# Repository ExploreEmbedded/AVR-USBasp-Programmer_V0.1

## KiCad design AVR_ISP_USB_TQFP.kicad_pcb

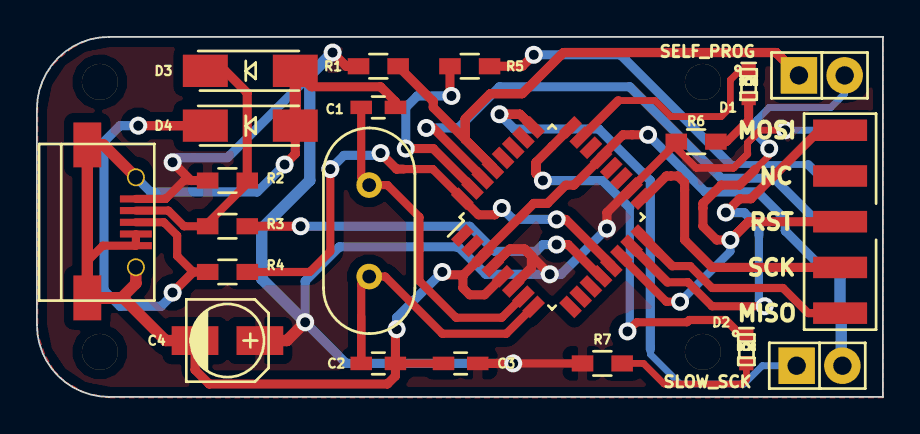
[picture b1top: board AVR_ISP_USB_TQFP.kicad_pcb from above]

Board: 2 copper layers, 47.0 x 20.0 mm, 26 parts (1 on the bottom side), 21 nets.

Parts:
C1, C2: 22pF; C_0603_HandSoldering
C3: 0.1uF; C_0603_HandSoldering
C4: 4.7uF; c_elec_4x5.8
CON1: USB-MICRO-B; USB_Micro-B_SMD
D1: RED; LED-0603_NEW
D2: GREEN; LED-0603_NEW
D3, D4: 3.6V; ZenerDiode_SMD_new
IC1: ATMEGA8-AI; LQFP-32_7x7mm_Pitch0.8mm
JP1: SELF_PROG; Pin_Header_Straight_1x02
JP2: SLOW_SCK; Pin_Header_Straight_1x02
LOGO: LOGO (2)
P1: CONN_02X05; 5X2_FRC_2SIDE_EE
P2, P3, P4, P5: CONN_01X01; 1pin
R1: 10K; R_0603_HandSoldering
R2: 2.2K; R_0603_HandSoldering
R3, R4: 68E; R_0603_HandSoldering
R5, R6, R7: 1k; R_0603_HandSoldering
X1: 12MHz; HC-49V

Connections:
GND: C1.2, C2.2, C3.1, C4.2, CON1.4, CON1.5, CON1.6, CON1.7, CON1.8, CON1.9, D3.1, D4.1, IC1.3, IC1.5, IC1.21, JP2.2, P1.8, P1.10
unnamed: C1.1, IC1.7, X1.1
unnamed: C2.1, IC1.8, X1.2
unnamed: CON1.2, D3.2, R2.2, R3.1
unnamed: CON1.3, D4.2, R4.1
unnamed: D1.1, R6.2
unnamed: D1.2, IC1.23
unnamed: D2.1, R7.2
unnamed: D2.2, IC1.24
unnamed: IC1.12, R3.2
unnamed: IC1.13, IC1.32, R4.2
unnamed: IC1.14, JP1.2, P1.5
unnamed: IC1.15, P1.1
unnamed: IC1.16, P1.9
unnamed: IC1.17, P1.7
unnamed: IC1.25, JP2.1
unnamed: IC1.29, JP1.1, R1.1
unnamed: IC1.30, P1.6
unnamed: IC1.31, R5.2
unnamed: P1.4, R5.1
VCC: C3.2, C4.1, CON1.1, IC1.4, IC1.6, IC1.18, P1.2, R1.2, R2.1, R6.1, R7.1

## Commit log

2015-09-11 Started Schematic
2015-09-22 added complete layout
2015-09-23 final
2015-09-23 final_v1
2015-09-25 changes done as per powerPCB
2015-09-25 Gerber file updated
2015-10-12 Changed legend
2015-10-12 gerber file
    Gerber file for prototype
2015-10-12 Final Gerber
    Final gerber data generated
2016-09-27 Folder structured
2016-09-27 BOM generated
